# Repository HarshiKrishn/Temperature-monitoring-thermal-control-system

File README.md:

# Temperature Monitoring and Thermal Control System

This project implements a **microcontroller-based temperature monitoring and control system** using Arduino.  
The system measures temperature using a sensor, displays the real-time value on a **16x2 LCD**, and automatically activates a **cooling fan** when the temperature exceeds a defined threshold.

The goal is to maintain the system temperature within the safe range **25°C – 50°C**.

---

## Project Overview

The system continuously reads temperature data from the sensor through the Arduino’s ADC.  
Based on the measured temperature, the controller determines the operating state and controls a cooling fan.

Three LEDs provide visual indication of the system status.

---

## System Features

- Real-time temperature monitoring  
- LCD temperature display  
- Automatic cooling fan control  
- LED status indicators  
- Overheat warning system  
- Simulation using **TinkerCAD**  
- Custom **PCB design using KiCad**

---

## Temperature Control Logic

| Temperature Range | Fan Status | LED Indicator | System State |
|------------------|------------|--------------|-------------|
| < 25°C | OFF | Green LED | Safe |
| 25°C – 50°C | ON | Yellow LED | Normal |
| > 50°C | ON | Red LED | Overheat |

---

## Hardware Components

- Arduino / ATmega328P
- Temperature sensor
- 16x2 LCD display
- DC cooling fan
- NPN transistor (fan driver)
- Flyback diode
- Status LEDs (Green, Yellow, Red)
- Resistors
- Potentiometer (LCD contrast)

---

## System Architecture

Temperature Sensor → Arduino ADC → Control Logic →  
LCD Display + Fan Driver + Status LEDs

---

## Simulation

The system was first validated using **TinkerCAD simulation** to verify:

- Temperature sensing
- LCD display output
- Automatic fan activation
- LED status indicators

Simulation results are available in the **images folder**.

---

## PCB Design

A custom PCB was designed using **KiCad**, including:

- Schematic design
- PCB layout
- ERC and DRC verification
- 3D PCB visualization

### PCB Schematic

### PCB Layout

### 3D PCB View

---

## System Operation

Example outputs:

**Safe Condition**
**Normal Condition**
**Overheat Condition**

## Tools Used

- Kicad(PCB design)
- Tinkercad (Circuit Simulation)
- Github( Version Control and project hasting)

## 👤 Author

Designed and developed by Harshini  
Embedded Systems & PCB Design Enthusiast

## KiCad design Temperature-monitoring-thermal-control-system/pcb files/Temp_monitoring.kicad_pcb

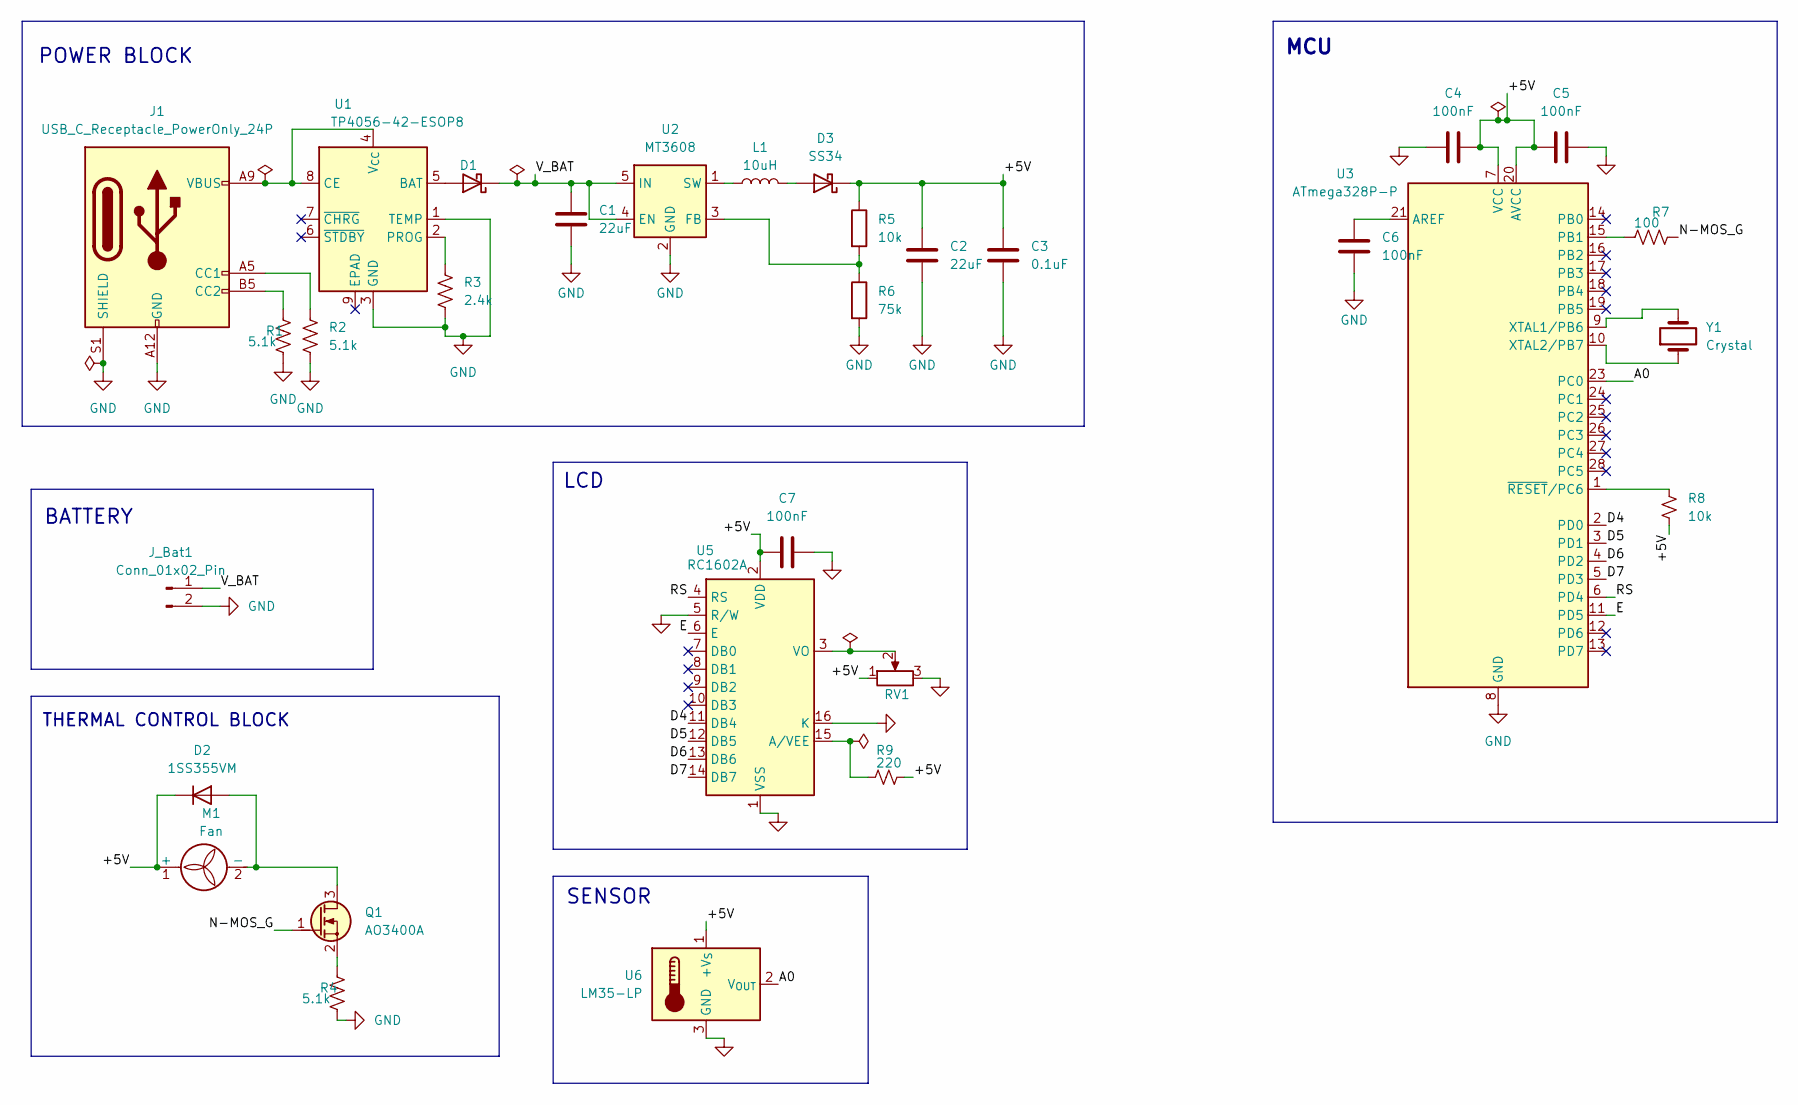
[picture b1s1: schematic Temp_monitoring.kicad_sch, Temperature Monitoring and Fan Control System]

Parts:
C1, C2: 22uF; C_1206_3216Metric
C3: 0.1uF; C_0603_1608Metric
C4, C5, C7: 100nF; C_0603_1608Metric
C6: 100nF; C_1206_3216Metric
D1: SS14; D_SMA_Handsoldering
D2: 1SS355VM; D_SOD-323F
D3: SS34; D_SMA
J1: USB_C_Receptacle_PowerOnly_24P; USB_C_Receptacle_HRO_TYPE-C-31-M-12
J_Bat1: Conn_01x02_Pin; JST_PH_S2B-PH-K_1x02_P2.00mm_Horizontal
L1: 10uH; L_6.3x6.3_H3
M1: Fan; PinHeader_1x02_P2.54mm_Vertical
Q1: AO3400A; SOT-23
R1: 5.1k; R_0603_1608Metric
R2, R4: 5.1k; R_0603_1608Metric_Pad0.98x0.95mm_HandSolder
R3: 2.4k; R_0603_1608Metric_Pad0.98x0.95mm_HandSolder
R5: 10k; R_1206_3216Metric
R6: 75k; R_1206_3216Metric
R7: 100; R_0603_1608Metric_Pad0.98x0.95mm_HandSolder
R8: 10k; R_0603_1608Metric
R9: 220; R_0603_1608Metric
RV1: R_Potentiometer; Potentiometer_Bourns_3299W_Vertical
U1: TP4056-42-ESOP8; SOIC-8-1EP_3.9x4.9mm_P1.27mm_EP2.41x3.3mm_ThermalVias
U2: MT3608; SOT-23-6
U3: ATmega328P-P; DIP-28_W7.62mm
U5: RC1602A
U6: LM35-LP; TO-92_Inline
Y1: Crystal; Crystal_HC49-4H_Vertical

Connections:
/+5V: C2.1, C3.1, C4.2, C5.1, C7.1, D2.1 (K), D3.1 (K), M1.1 (+), R5.1, R8.2, R9.2, RV1.1, U3.7 (VCC), U3.20 (AVCC), U5.2 (VDD), U6.1 (+V_{S}); also elsewhere on the board
/A0: U3.23 (PC0), U6.2 (V_{OUT}); also elsewhere on the board
/D4: U3.2 (PD0), U5.11 (DB4)
/D5: U3.3 (PD1), U5.12 (DB5)
/D6: U3.4 (PD2), U5.13 (DB6)
/D7: U3.5 (PD3), U5.14 (DB7)
/E: U3.11 (PD5), U5.6 (E)
/N-MOS_G: Q1.1 (G), R7.1
/RS: U3.6 (PD4), U5.4 (RS)
/V_BAT: C1.1, D1.1 (K), J_Bat1.1, U2.4 (EN), U2.5 (IN)
GND: C1.2, C2.2, C3.2, C4.1, C5.2, C6.2, C7.2, J1.A1 (GND), J1.A12 (GND), J1.B1 (GND), J1.B12 (GND), J1.S1 (SHIELD), J_Bat1.2, R1.1, R2.1, R3.2, R4.1, R6.2, RV1.3, U1.1 (TEMP), U1.3 (GND), U2.2 (GND), U3.8 (GND), U3.22 (GND), U5.1 (VSS), U5.5 (R/W), U5.16 (K), U6.3 (GND); also elsewhere on the board
unnamed: D1.2 (A), U1.5 (BAT)
unnamed 12: D2.2 (A), M1.2 (-), Q1.3 (D); also elsewhere on the board
unnamed: D3.2 (A), L1.2
unnamed: J1.A5 (CC1), R2.2
unnamed: J1.B5 (CC2), R1.2
unnamed: Q1.2 (S), R4.2
unnamed: J1.A4 (VBUS), J1.A9 (VBUS), J1.B4 (VBUS), J1.B9 (VBUS), U1.4 (V_{CC}), U1.8 (CE)
unnamed: R3.1, U1.2 (PROG)
unnamed: R5.2, R6.1, U2.3 (FB)
unnamed: L1.1, U2.1 (SW)
unnamed: C6.1, U3.21 (AREF)
unnamed: R7.2, U3.15 (PB1)
unnamed: U3.9 (XTAL1/PB6), Y1.2
unnamed: U3.10 (XTAL2/PB7), Y1.1
unnamed: R8.1, U3.1 (~RESET/PC6)
unnamed: R9.1, U5.15 (A/VEE)
unnamed: RV1.2, U5.3 (VO)

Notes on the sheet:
SENSOR
BATTERY
POWER BLOCK
MCU
THERMAL CONTROL BLOCK
LCD

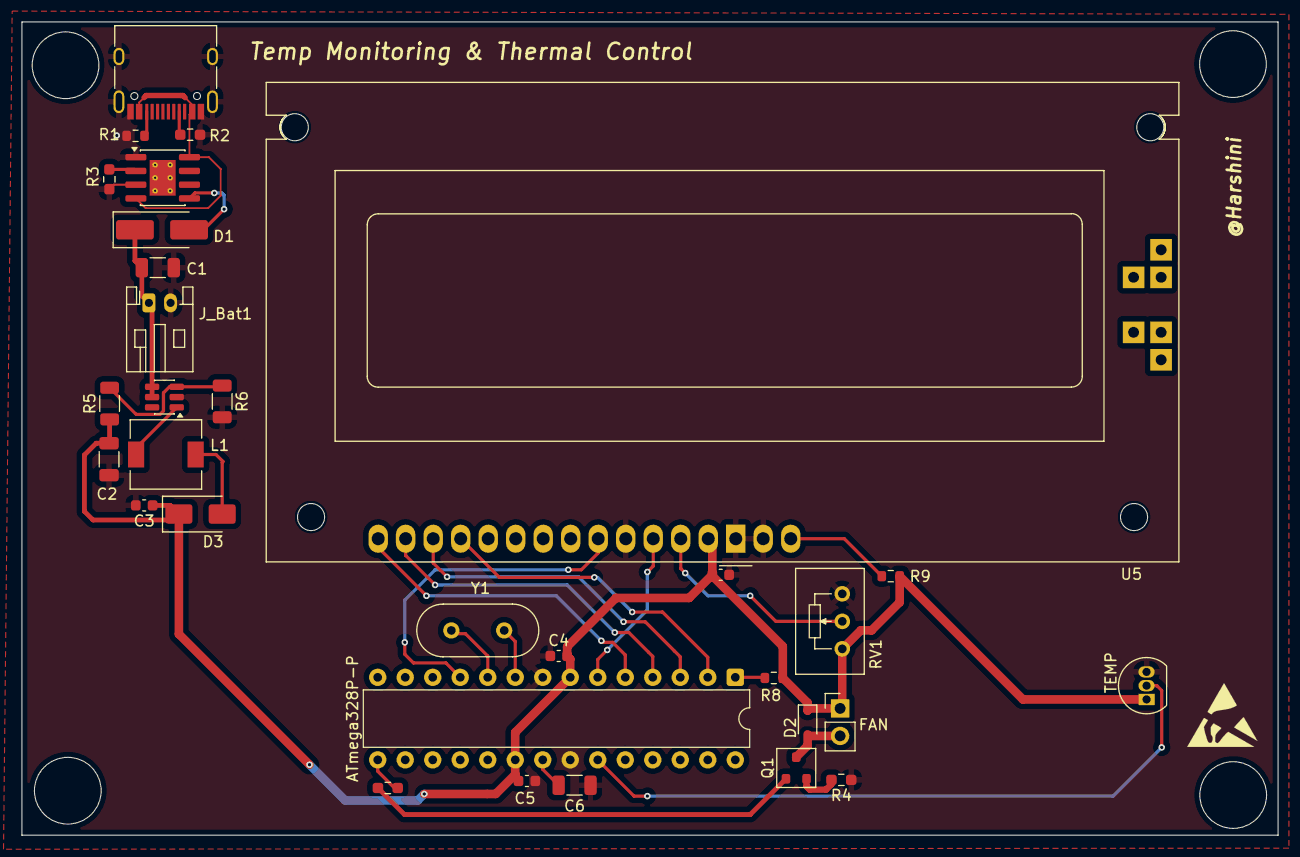
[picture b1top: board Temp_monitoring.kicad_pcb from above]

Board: 2 copper layers, 116.0 x 75.1 mm, 31 parts (0 on the bottom side), 28 nets.

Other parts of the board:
FAN: Fan; PinHeader_1x02_P2.54mm_Vertical
TEMP: LM35-LP; TO-92_Inline

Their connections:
/+5V: FAN.1 (+), TEMP.1 (+V_{S}); also elsewhere on the board
/A0: TEMP.2 (V_{OUT}); also elsewhere on the board
GND: TEMP.3 (GND); also elsewhere on the board
unnamed 12: FAN.2 (-); also elsewhere on the board

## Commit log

2026-03-13 Add Temperature monitoring and thermal control system project
    Includes Arduino code,Simulation results, project report, and Kicad PCB design
2026-03-13 Add README for temperature monitoring system
    This README provides an overview of a microcontroller-based temperature monitoring and control system, detailing its features, components, architecture, simulation, and PCB design.
2026-03-13 Include PCB schematic image in README
    Added PCB schematic image to the README.
